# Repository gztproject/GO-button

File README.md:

# GO-button

A programmable 5-button RGB macro keypad

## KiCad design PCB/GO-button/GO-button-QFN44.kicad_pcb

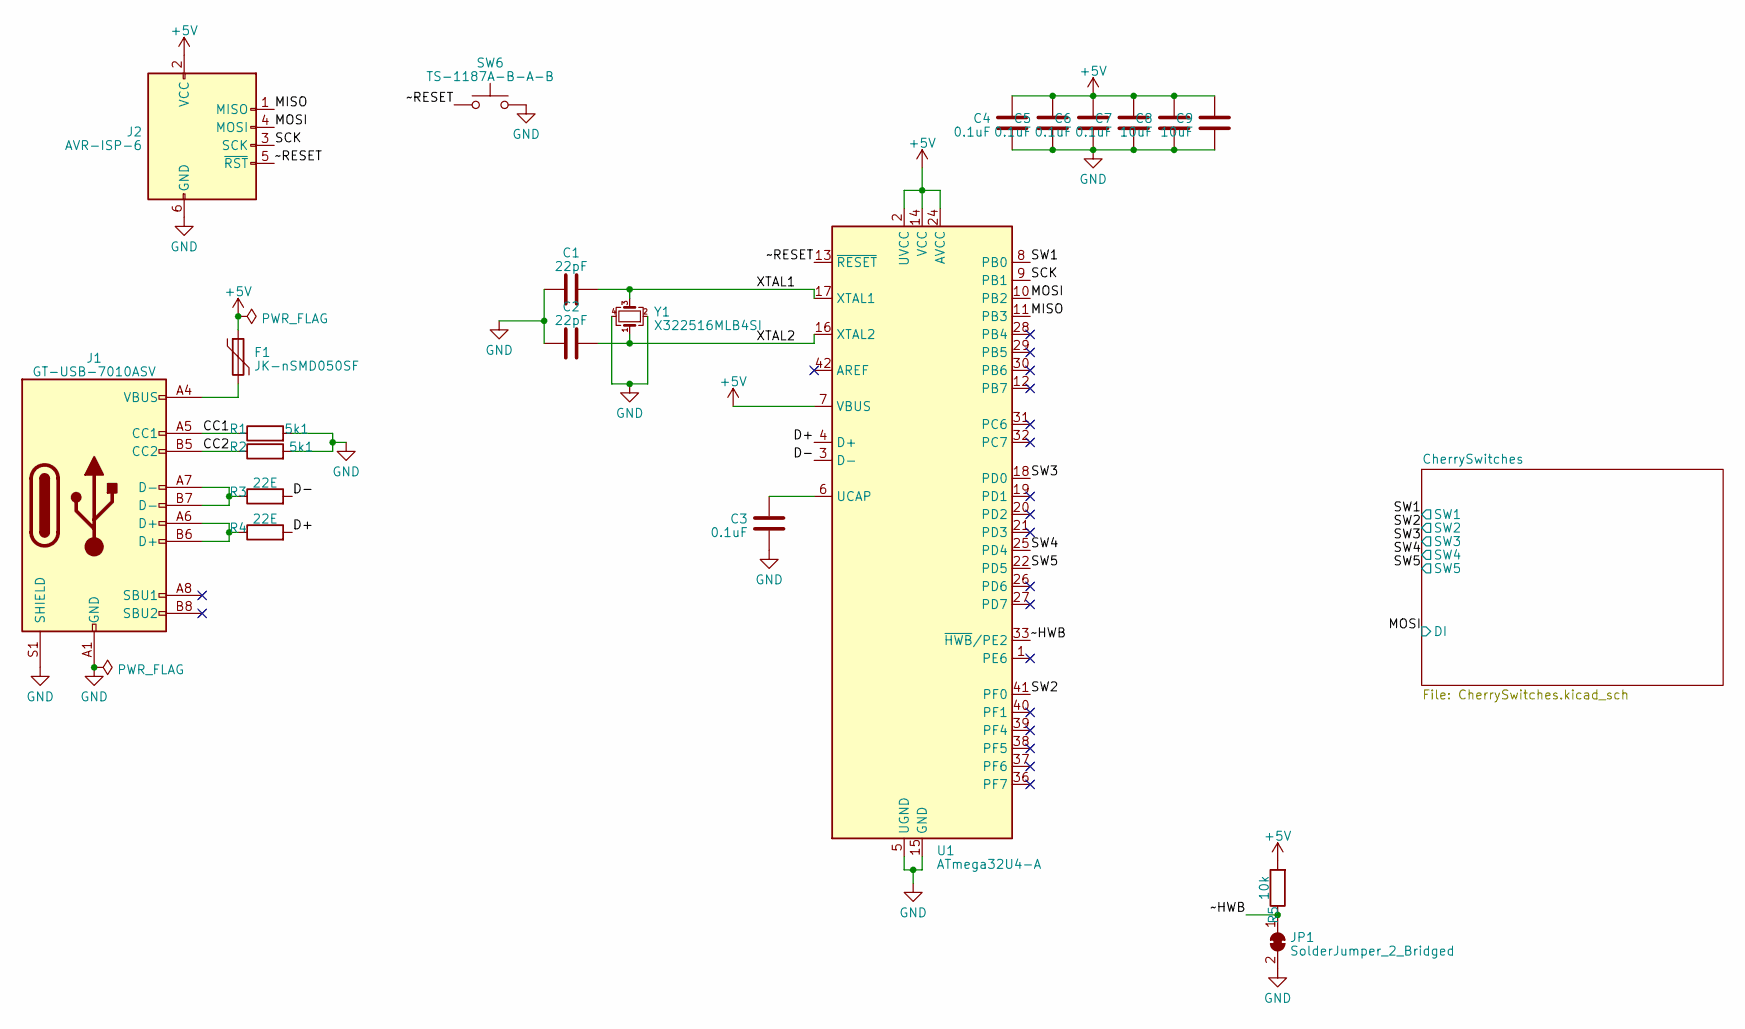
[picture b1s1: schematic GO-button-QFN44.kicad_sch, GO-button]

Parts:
C1, C2: 22pF; C_0402_1005Metric
C3, C4, C5, C6, C7: 0.1uF; C_0402_1005Metric
C8, C9: 10uF; C_0402_1005Metric
F1: JK-nSMD050SF; Fuse_1206_3216Metric
J1: GT-USB-7010ASV; USB_C_Receptacle_G-Switch_GT-USB-7010ASV
J2: AVR-ISP-6; AVR_ISP_HEADER
JP1: SolderJumper_2_Bridged; SolderJumper-2_P1.3mm_Bridged_RoundedPad1.0x1.5mm
R1, R2: 5k1; R_0402_1005Metric
R3, R4: 22E; R_0402_1005Metric
R5: 10k; R_0402_1005Metric
SW6: TS-1187A-B-A-B; SW_SPST_TL3342
U1: ATmega32U4-A; QFN-44-1EP_7x7mm_P0.5mm_EP5.2x5.2mm_ThermalVias
Y1: X322516MLB4SI; Crystal_SMD_3225-4Pin_3.2x2.5mm

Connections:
+5V: C4.2, C5.2, C6.2, C7.2, C8.2, C9.2, F1.1, J2.2 (VCC), R5.2, U1.2 (UVCC), U1.7 (VBUS), U1.14 (VCC), U1.24 (AVCC), U1.34 (VCC), U1.44 (AVCC); also elsewhere on the board
/CC1: J1.A5 (CC1), R1.1
/CC2: J1.B5 (CC2), R2.1
/D+: R4.2, U1.4 (D+)
/D-: R3.2, U1.3 (D-)
/MISO: J2.1 (MISO), U1.11 (PB3)
/MOSI: J2.4 (MOSI), U1.10 (PB2); also elsewhere on the board
/SCK: J2.3 (SCK), U1.9 (PB1)
/SW1: U1.8 (PB0); also elsewhere on the board
/SW2: U1.41 (PF0); also elsewhere on the board
/SW3: U1.18 (PD0); also elsewhere on the board
/SW4: U1.25 (PD4); also elsewhere on the board
/SW5: U1.22 (PD5); also elsewhere on the board
/XTAL1: C1.2, U1.17 (XTAL1), Y1.3
/XTAL2: C2.2, U1.16 (XTAL2), Y1.1
/~HWB: JP1.1 (A), R5.1, U1.33 (~HWB/PE2)
/~RESET: J2.5 (~RST), SW6.1, U1.13 (~RESET)
GND: C1.1, C2.1, C3.1, C4.1, C5.1, C6.1, C7.1, C8.1, C9.1, J1.A1 (GND), J1.A12 (GND), J1.B1 (GND), J1.B12 (GND), J1.S1 (SHIELD), J2.6 (GND), JP1.2 (B), R1.2, R2.2, SW6.2, U1.5 (UGND), U1.15 (GND), U1.23 (GND), U1.35 (GND), U1.43 (GND), Y1.2, Y1.4; also elsewhere on the board
unnamed: F1.2, J1.A4 (VBUS), J1.A9 (VBUS), J1.B4 (VBUS), J1.B9 (VBUS)
unnamed: J1.A6 (D+), J1.B6 (D+), R4.1
unnamed: J1.A7 (D-), J1.B7 (D-), R3.1
unnamed: C3.2, U1.6 (UCAP)

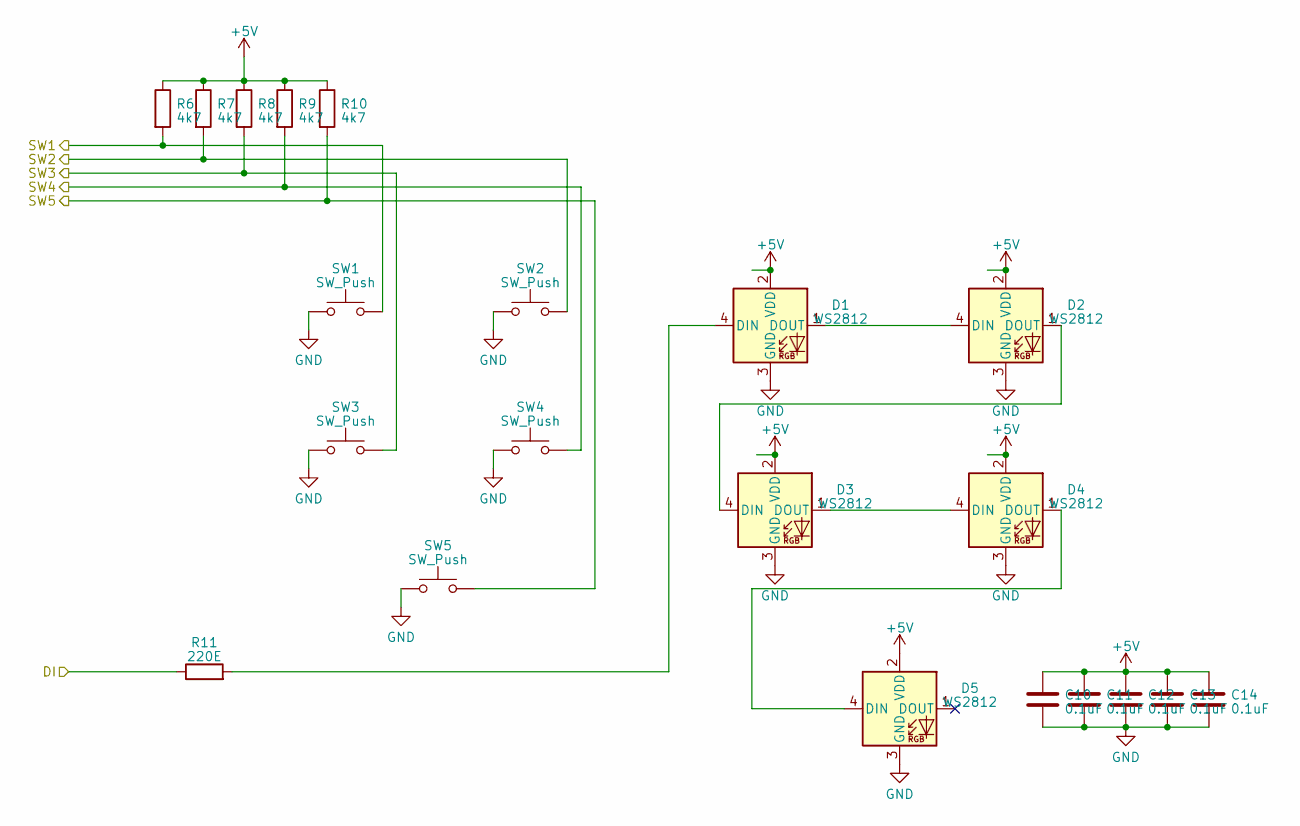
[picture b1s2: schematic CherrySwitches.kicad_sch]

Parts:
C10, C11, C12, C13, C14: 0.1uF; C_0402_1005Metric
D1, D2, D3, D4, D5: WS2812; XL-1010RGBC-WS2812B
R6, R7, R8, R9, R10: 4k7; R_0402_1005Metric
R11: 220E; R_0402_1005Metric
SW1, SW2, SW3, SW4, SW5: SW_Push; SW_Cherry_MX_PCB

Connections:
+5V: C10.1, C11.1, C12.1, C13.1, C14.1, D1.2 (VDD), D2.2 (VDD), D3.2 (VDD), D4.2 (VDD), D5.2 (VDD), R6.1, R7.1, R8.1, R9.1, R10.1; also elsewhere on the board
/MOSI: R11.1; also elsewhere on the board
/SW1: R6.2, SW1.2; also elsewhere on the board
/SW2: R7.2, SW2.2; also elsewhere on the board
/SW3: R8.2, SW3.2; also elsewhere on the board
/SW4: R9.2, SW4.2; also elsewhere on the board
/SW5: R10.2, SW5.2; also elsewhere on the board
GND: C10.2, C11.2, C12.2, C13.2, C14.2, D1.3 (GND), D2.3 (GND), D3.3 (GND), D4.3 (GND), D5.3 (GND), SW1.1, SW2.1, SW3.1, SW4.1, SW5.1; also elsewhere on the board
unnamed: D1.4 (DIN), R11.2
unnamed: D1.1 (DOUT), D2.4 (DIN)
unnamed: D2.1 (DOUT), D3.4 (DIN)
unnamed: D3.1 (DOUT), D4.4 (DIN)
unnamed: D4.1 (DOUT), D5.4 (DIN)

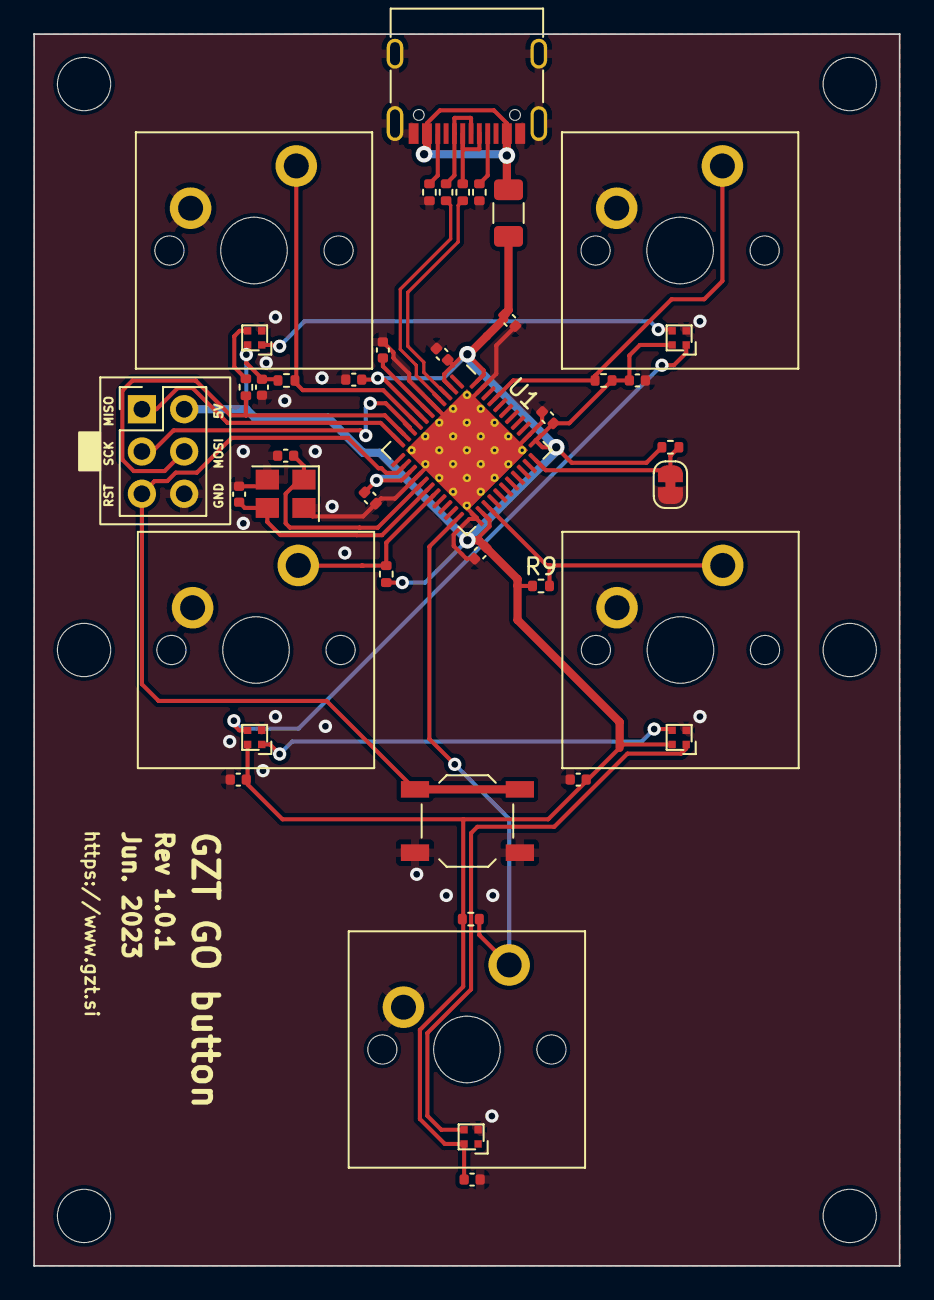
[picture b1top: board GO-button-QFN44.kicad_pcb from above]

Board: 2 copper layers, 52.0 x 74.0 mm, 42 parts (0 on the bottom side), 27 nets.

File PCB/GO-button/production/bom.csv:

Designator,Footprint,Quantity,Value,LCSC Part #
"C1, C2",0402,2,22pF,
"C10, C11, C12, C13, C14, C3, C4, C5, C6, C7",0402,10,0.1uF,
"C8, C9",0402,2,10uF,
"D1, D2, D3, D4, D5",XL-1010RGBC-WS2812B,5,WS2812,
F1,1206,1,JK-nSMD050SF,
J1,USB_C_Receptacle_G-Switch_GT-USB-7010ASV,1,GT-USB-7010ASV,
J2,AVR_ISP_HEADER,1,AVR-ISP-6,
JP1,SolderJumper-2_P1.3mm_Bridged_RoundedPad1.0x1.5mm,1,SolderJumper_2_Bridged,
"R1, R2",0402,2,5k1,
"R10, R6, R7, R8, R9",0402,5,4k7,
R11,0402,1,220E,
"R3, R4",0402,2,22E,
R5,0402,1,10k,
"SW1, SW2, SW3, SW4, SW5",SW_Cherry_MX_PCB,5,SW_Push,
SW6,SW_SPST_TL3342,1,TS-1187A-B-A-B,
U1,QFN-44-1EP_7x7mm_P0.5mm_EP5.2x5.2mm_ThermalVias,1,ATmega32U4-A,
Y1,Crystal_SMD_3225-4Pin_3.2x2.5mm,1,X322516MLB4SI,

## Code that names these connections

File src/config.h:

#ifndef _CONFIG_H
#define _CONFIG_H

#define SERIAL_RX_BUFFER_SIZE 128
#define SERIAL_TX_BUFFER_SIZE 128

#define SERIAL_DEBUG 0
#define KEYPAD_DEBUG 0
#define PRESET_DEBUG 0

#define NUM_BUTTONS 5
#define NUM_PRESETS NUM_BUTTONS

#define BTN_0_PIN 17  //PB0
#define BTN_1_PIN 23  //PF0
#define BTN_2_PIN 3   //PD0
#define BTN_3_PIN 4   //PD4
#define BTN_4_PIN 30  //PD5

#define LED_PIN 16  // PB2 - MOSI

#define LED_LOW_INT 51
#define LED_HIGH_INT 173

#define MIDI_CH 0
#define MIDI_VELOCITY 127

#define DEFAULT_PRESET 0

//Preset 0
#define P0_COL GREEN
#define P0_NAME "MIDI"
#define P0_MODE HwMode::MIDI_MODE
#define P0B0_KEY 47
#define P0B0_COL BLUE
#define P0B1_KEY 48
#define P0B1_COL BLUE
#define P0B2_KEY 50
#define P0B2_COL YELLOW
#define P0B3_KEY 52
#define P0B3_COL RED
#define P0B4_KEY 53
#define P0B4_COL GREEN

#define DEFAULT_TIMEOUT 3000

//Preset 1
#define P1_COL RED
#define P1_NAME "KEYBOARD"
#define P1_MODE HwMode::KB_MODE
#define P1B0_KEY KEY_UP_ARROW
#define P1B0_COL BLUE
#define P1B1_KEY KEY_DOWN_ARROW
#define P1B1_COL BLUE
#define P1B2_KEY KEY_P
#define P1B2_COL YELLOW
#define P1B3_KEY KEY_ESC
#define P1B3_COL RED
#define P1B4_KEY KEY_SPACE
#define P1B4_COL GREEN

//Preset 2
#define P2_COL PURPLE
#define P2_NAME "HID"
#define P2_MODE HwMode::HID_MODE
#define P2B0_KEY MEDIA_VOL_DOWN
#define P2B0_COL BLUE
#define P2B1_KEY MEDIA_VOL_UP
#define P2B1_COL BLUE
#define P2B2_KEY MEDIA_PREVIOUS
#define P2B2_COL GREEN
#define P2B3_KEY MEDIA_NEXT
#define P2B3_COL GREEN
#define P2B4_KEY MEDIA_PLAY_PAUSE
#define P2B4_COL RED

//Preset 3
#define P3_COL PURPLE
#define P3_NAME "HID"
#define P3_MODE HwMode::HID_MODE
#define P3B0_KEY MEDIA_VOL_DOWN
#define P3B0_COL BLUE
#define P3B1_KEY MEDIA_VOL_UP
#define P3B1_COL BLUE
#define P3B2_KEY MEDIA_PREVIOUS
#define P3B2_COL GREEN
#define P3B3_KEY MEDIA_NEXT
#define P3B3_COL GREEN
#define P3B4_KEY MEDIA_PLAY_PAUSE
#define P3B4_COL RED

//Preset 4
#define P4_COL PURPLE
#define P4_NAME "HID"
#define P4_MODE HwMode::HID_MODE
#define P4B0_KEY MEDIA_VOL_DOWN
#define P4B0_COL BLUE
#define P4B1_KEY MEDIA_VOL_UP
#define P4B1_COL BLUE
#define P4B2_KEY MEDIA_PREVIOUS
#define P4B2_COL GREEN
#define P4B3_KEY MEDIA_NEXT
#define P4B3_COL GREEN
#define P4B4_KEY MEDIA_PLAY_PAUSE
#define P4B4_COL RED

#endif

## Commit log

2021-10-02 Inital commit
2021-10-02 Extracted button in a separate class
2021-10-03 Added MIDI support
2023-05-16 Updated PCB, switched libraries, code fixes
2023-05-18 Flashing bugfix
2023-05-18 LED bugfix
2023-05-18 Added some color stuff
2023-05-20 Restructuring
2023-05-20 More work
2023-05-21 It builds!
2023-05-21 Took out the settings
2023-06-17 PCB REV 1.0.1
2023-06-18 Removed settings, shorter buffers
2023-06-18 Bugfixes, presets
2023-06-18 Cleanup
2023-06-19 Bugfixes
2023-06-20 Added board def to the project
2023-06-20 Added build action
2023-06-20 Fixed the custom bord variant
2023-06-21 Documentation
2023-06-24 Persisting
2023-06-26 Saving default preset
2023-06-26 Better startup sequence
2024-01-22 Added documentation, fixes
2024-01-22 more docs
2024-01-22 Docs auto build
2024-01-22 Fixed theme
2024-01-22 More autodoc stuff
2024-01-22 Documentation changes
2024-01-22 Added docs
2024-01-22 Added link to library
2024-01-22 typo
2024-01-22 Disclaimer
2024-01-22 Docs more aded I did
2024-02-04 Added soldering jig
2024-02-10 Added basic serial API
2024-02-11 Major code cleanup, fixes, lots of docs...
2024-02-12 Fixed update manual
2024-02-14 SetDefault fix, added changelog
2024-02-14 Quickfix
2024-02-14 docs
2024-06-16 Compiled custom bootloader
2024-06-20 Started a simple POC
2024-06-20 Added quick visualisation
2024-06-22 A bit of UX and a lot of reading
2024-06-22 Working on it
2024-06-23 Key functions mapping
2024-06-23 Enum fix
2024-06-23 Fixed enum
2024-06-23 Key functions setting is working
2026-03-15 3D files
2026-03-15 HTML configurator
